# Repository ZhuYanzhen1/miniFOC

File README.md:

&nbsp;&nbsp;&nbsp;&nbsp;&nbsp;&nbsp;&nbsp;&nbsp;&nbsp;&nbsp;&nbsp;&nbsp;&nbsp;&nbsp;&nbsp;&nbsp;English / [中文](./README_CN.md)

&nbsp;&nbsp;&nbsp;&nbsp;Are you still buying a DC brush motor drive module in about 3<span>$</span>? Are you still worried about the high noise in addition to the already low response speed and life? Allow me to present you our project, miniFOC---- a FOC brushless motor control scheme that can get you the most bang for your buck, for just 3 <span>$</span>!  **miniFOC** has a built-in torque closed-loop controller so that you can control a brushless motor with a 3-wire UART port. The software and hardware design are fully compliant with the AGPL-3.0 open source license.

**Note: This branch is still in the development stage. The hardware circuit has been designed and tested to be stable, yet the firmware is still under development. After the development of this branch is completed, it will provide current loop and non-inductive FOC features. At the same time, version 1.x.x will reach end of life (EOL) and will no longer be maintained. Version 2.x.x will no longer provide any compatibility with version 1.x.x**

***

### Brief Introduction

&nbsp;&nbsp;&nbsp;&nbsp;This open-source project aims to accomplish a FOC(Field Oriented Control) scheme that is operatable with minimum costs in China. The components selected in the example circuit are all manufactured in China. FOC possesses various advantages when it comes to controlling BLCD (Brushless Direct Current) motor; some of the benefits are as follows:

1. FOC has no speed limit at all and can be accurately controlled at any speed
2. FOC excels at its reversing performance, ensuring the smoothness of forward and reverse switching even when running at its highest speed
3. FOC can perform braking control in the form of energy recovery.
4. FOC can achieve three closed-loop control of torque, speed, and position.
5. FOC has significantly lower noise but much higher efficiency compared that of electric regulation

&nbsp;&nbsp;&nbsp;Although FOC has many advantages, its large amount of calculation and complex principles requires an expensive controller, which made FOC unpopular. After half a year’s research and iteration, I deeply optimized the part of the code that implements mass calculations and re-selected its components to fit the domestic supply chain. I hope this open-source project can help domestic developers use BLDC motors with excellent performance and contribute to the open-source community.

&nbsp;&nbsp;&nbsp;&nbsp;Since the miniFOC 1.X.X version was launched earlier (September 2021), after two years, many component supply chains have changed, making the miniFOC v1.X.X hardware no longer adaptable to new needs. Therefore, I re-selected based on the domestic supply chain, and added current loop and non-inductive FOC functions based on the previous one.

***

### Comparison Of Open Source Solutions

|    Open source solution    |   **miniFOC v2**   | [simpleFOC v2.0.4](https://github.com/simplefoc/Arduino-SimpleFOCShield) | [ODrive v3.6](https://github.com/odriverobotics/ODrive) | [FpOC](https://github.com/WangXuan95/FpOC) |
| :------------------------: | :----------: | :----------------------------------------------------------: | :------------------------------------------------: | :------------------------------------------------: |
|      Microcontroller       | CH32V203C8T6 |                          ATmega328P                          |                   STM32F405RGT6                    |               FPGA |
|        Driver chip         |    BDR2L00    |                            L6234                             |                      DRV8301                       |                      MP6540                 |
|     PID loop frequency     |    20kHz (typical)    |                   1kHz (typical)                        |                        8kHz (typical)                        |                        18kHz (typical)                        |
| Whether have current loop |      Yes      |                              Yes                              |                        Yes                         |                        Yes                      |
|       Driving power        |     400W     |                             120W                             |                        960W                        |                        90W                        |
|    Cost price (approx.)    |     3$     |                             [15$](https://www.simplefoc.com/simplefoc_shield_product)                             |                        [259$](https://odriverobotics.com/shop/odrive-v36)                        |                        20$                        |

&nbsp;&nbsp;&nbsp;&nbsp;As can be seen from the table above, the solution adopted by **miniFOC** can achieve high performance at low cost. At the same time, due to the re-selection based on the domestic supply chain, the selection of devices is not so limited and provides many alternatives. When the driving power reaches 400W, the cost of FOC can be reduced to about 3$, which also proves the degree of cost optimization and huge potential of this project.

***

### Performance Parameter 

+ Input voltage range: 6V ~ 24V (you can modify the circuit according to the tutorial [here]() to adapt to higher voltage).
+ Maximum driving current: 30A (you can modify the circuit according to the tutorial [here]() to achieve greater driving current).
+ Detailed parameters of FOC: Current loop close loop control, SVPWM (Space Vector Pulse Width Modulation) is adopted.
+ Communication parameters: UART baud rate is 115200, and [Mid Capacity Data Transmit Protocol](https://github.com/ZhuYanzhen1/CDTP/blob/master/mdtp/README.md) is used for data transmission.
+ Microcontroller parameters: RV32IMACXW core, 144MHz frequency, 64KB FLASH, 20KB SRAM. 

***

### Function Features

+ [x] Using space vector pulse width modulation
+ [x] Torque control without current sensor
+ [x] Rotational speed closed loop control
+ [x] Rotation angle closed loop control
+ [x] Automatic phase sequence detection and correction
+ [ ] Current loop closed loop control
+ [ ] Sensorless FOC algorithm

***

### Development Environment 

+ EDA Tool: KiCAD 7.0.8 (VC++ 1936, 64bit)
+ Compiler tool chain: riscv-none-elf-gcc 12.2.0 or riscv-none-embed-gcc 8.2.0
+ Programming tool: OpenOCD 0.11.0+dev-gfad123a16- (2023-07-03-15:11)
+ Integrated development tools: CLion 2023.2.2 #CL-232.9921.42
+ Software development tools: Qt 5.14.2 (MinGW 7.3.0 64bit)
+ Operating system and tool chain: 
  + Win10 + MinGW + CLion + riscv-none-elf-gcc + OpenOCD
  + Ubuntu22.04 + make + cmake + riscv-none-embed-gcc + OpenOCD

***

### Getting Started

+ You can visit the [Wiki page](https://github.com/ZhuYanzhen1/miniFOC/wiki) of this project for a getting started guide.
+ You can visit [Github Page](https://zhuyanzhen1.github.io/miniFOC/) to learn about the functions and variable usage in the code.
+ You can visit the [Release](https://github.com/ZhuYanzhen1/miniFOC/releases) page to get the latest firmware, monitor tools, and compilation tool chains.

***

### Bugs & Feature Requests

Please report bugs and request features using the [Issue Tracker](https://github.com/ZhuYanzhen1/miniFOC/issues) and follow these request:

1. Before publishing an Issue, please check whether the existing Issue contains your question or request. If so, please try to solve it first according to the solution in the Issue.
2. When publishing an Issue, please provide your operating environment and write down the reproduction method in detail.
3. For discussions on non-operational bugs, please start them in [Discussion](https://github.com/ZhuYanzhen1/miniFOC/discussions) and do not submit them to Issues.

***

### License

The source code is released under a [AGPL-3.0 License](https://github.com/ZhuYanzhen1/miniFOC/blob/main/LICENSE).

**Affiliation：AcmeTech<br>
Author: Yanzhen Zhu<br>
Maintainer：YanzhenZhu, 2208213223@qq.com**

&nbsp;&nbsp;&nbsp;&nbsp;The project has been tested under Windows 10 and Ubuntu 22.04 LTS. This is research code, expect that it changes often and any fitness for a particular purpose is disclaimed.

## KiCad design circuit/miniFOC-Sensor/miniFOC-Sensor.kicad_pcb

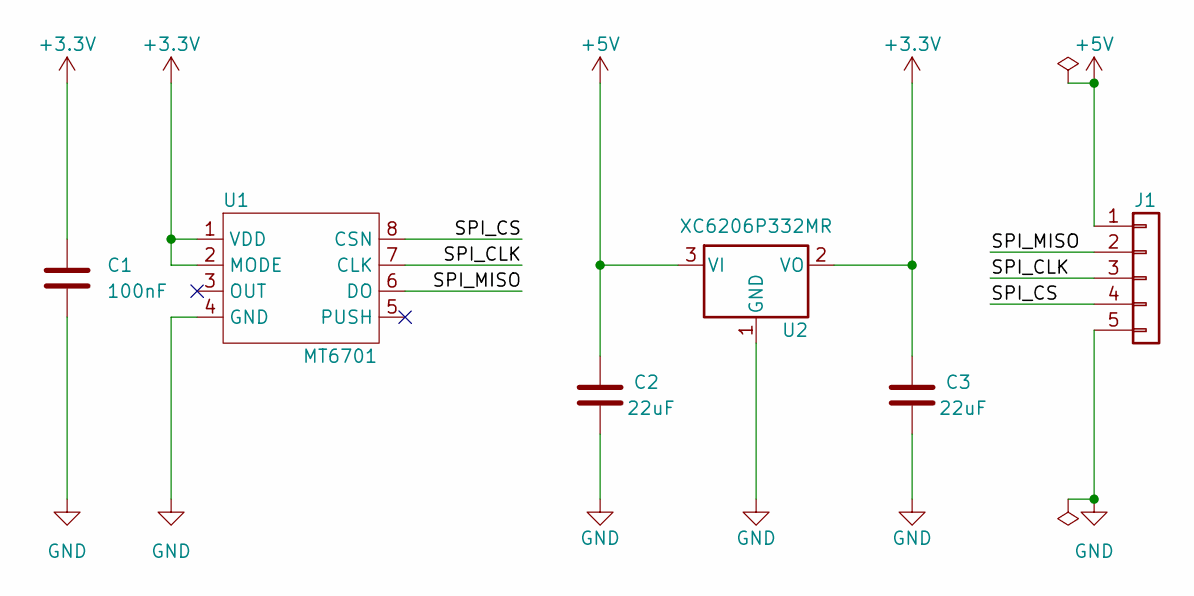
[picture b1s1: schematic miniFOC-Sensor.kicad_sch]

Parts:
C1: 100nF; C_0402_1005Metric
C2, C3: 22uF; C_0603_1608Metric
J1: Conn_01x05; JST_GH_SM05B-GHS-TB_1x05-1MP_P1.25mm_Horizontal
U1: MT6701; SOP-8_3.9x4.9mm_P1.27mm
U2: XC6206P332MR; SOT-23

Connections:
+3.3V: C1.1, C3.2, U1.1 (VDD), U1.2 (MODE), U2.2 (VO)
+5V: C2.2, J1.1, U2.3 (VI)
/SPI_CLK: J1.3, U1.7 (CLK)
/SPI_CS: J1.4, U1.8 (CSN)
/SPI_MISO: J1.2, U1.6 (DO)
GND: C1.2, C2.1, C3.1, J1.5, U1.4 (GND), U2.1 (GND)

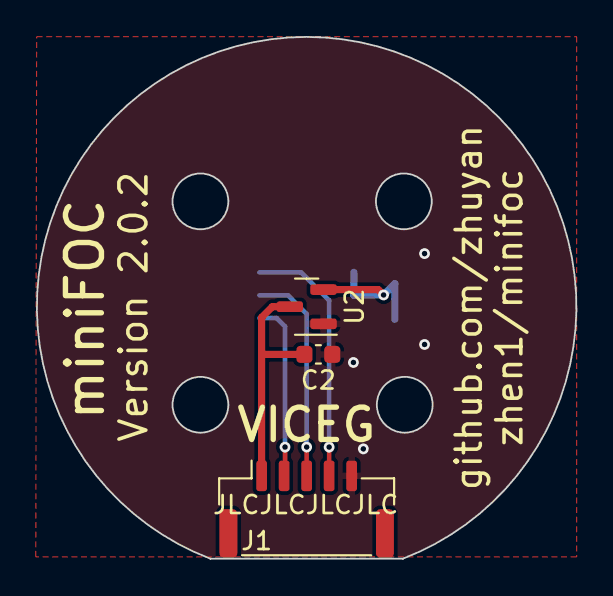
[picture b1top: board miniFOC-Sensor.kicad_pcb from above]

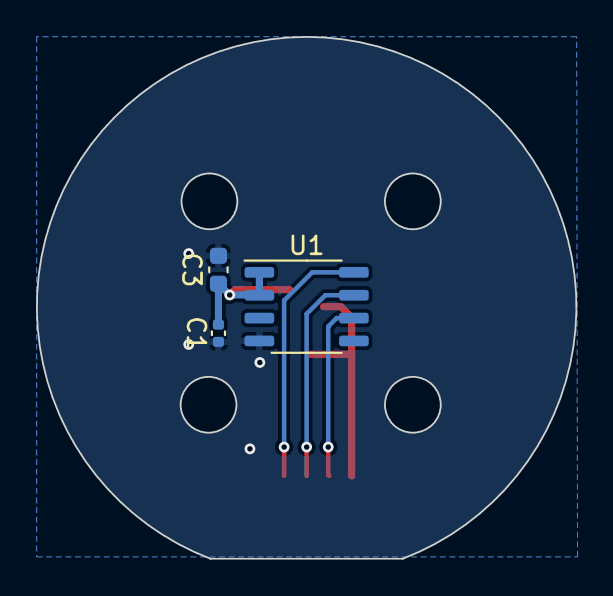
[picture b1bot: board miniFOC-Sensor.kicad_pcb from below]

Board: 2 copper layers, 30.0 x 29.0 mm, 6 parts (3 on the bottom side), 6 nets.

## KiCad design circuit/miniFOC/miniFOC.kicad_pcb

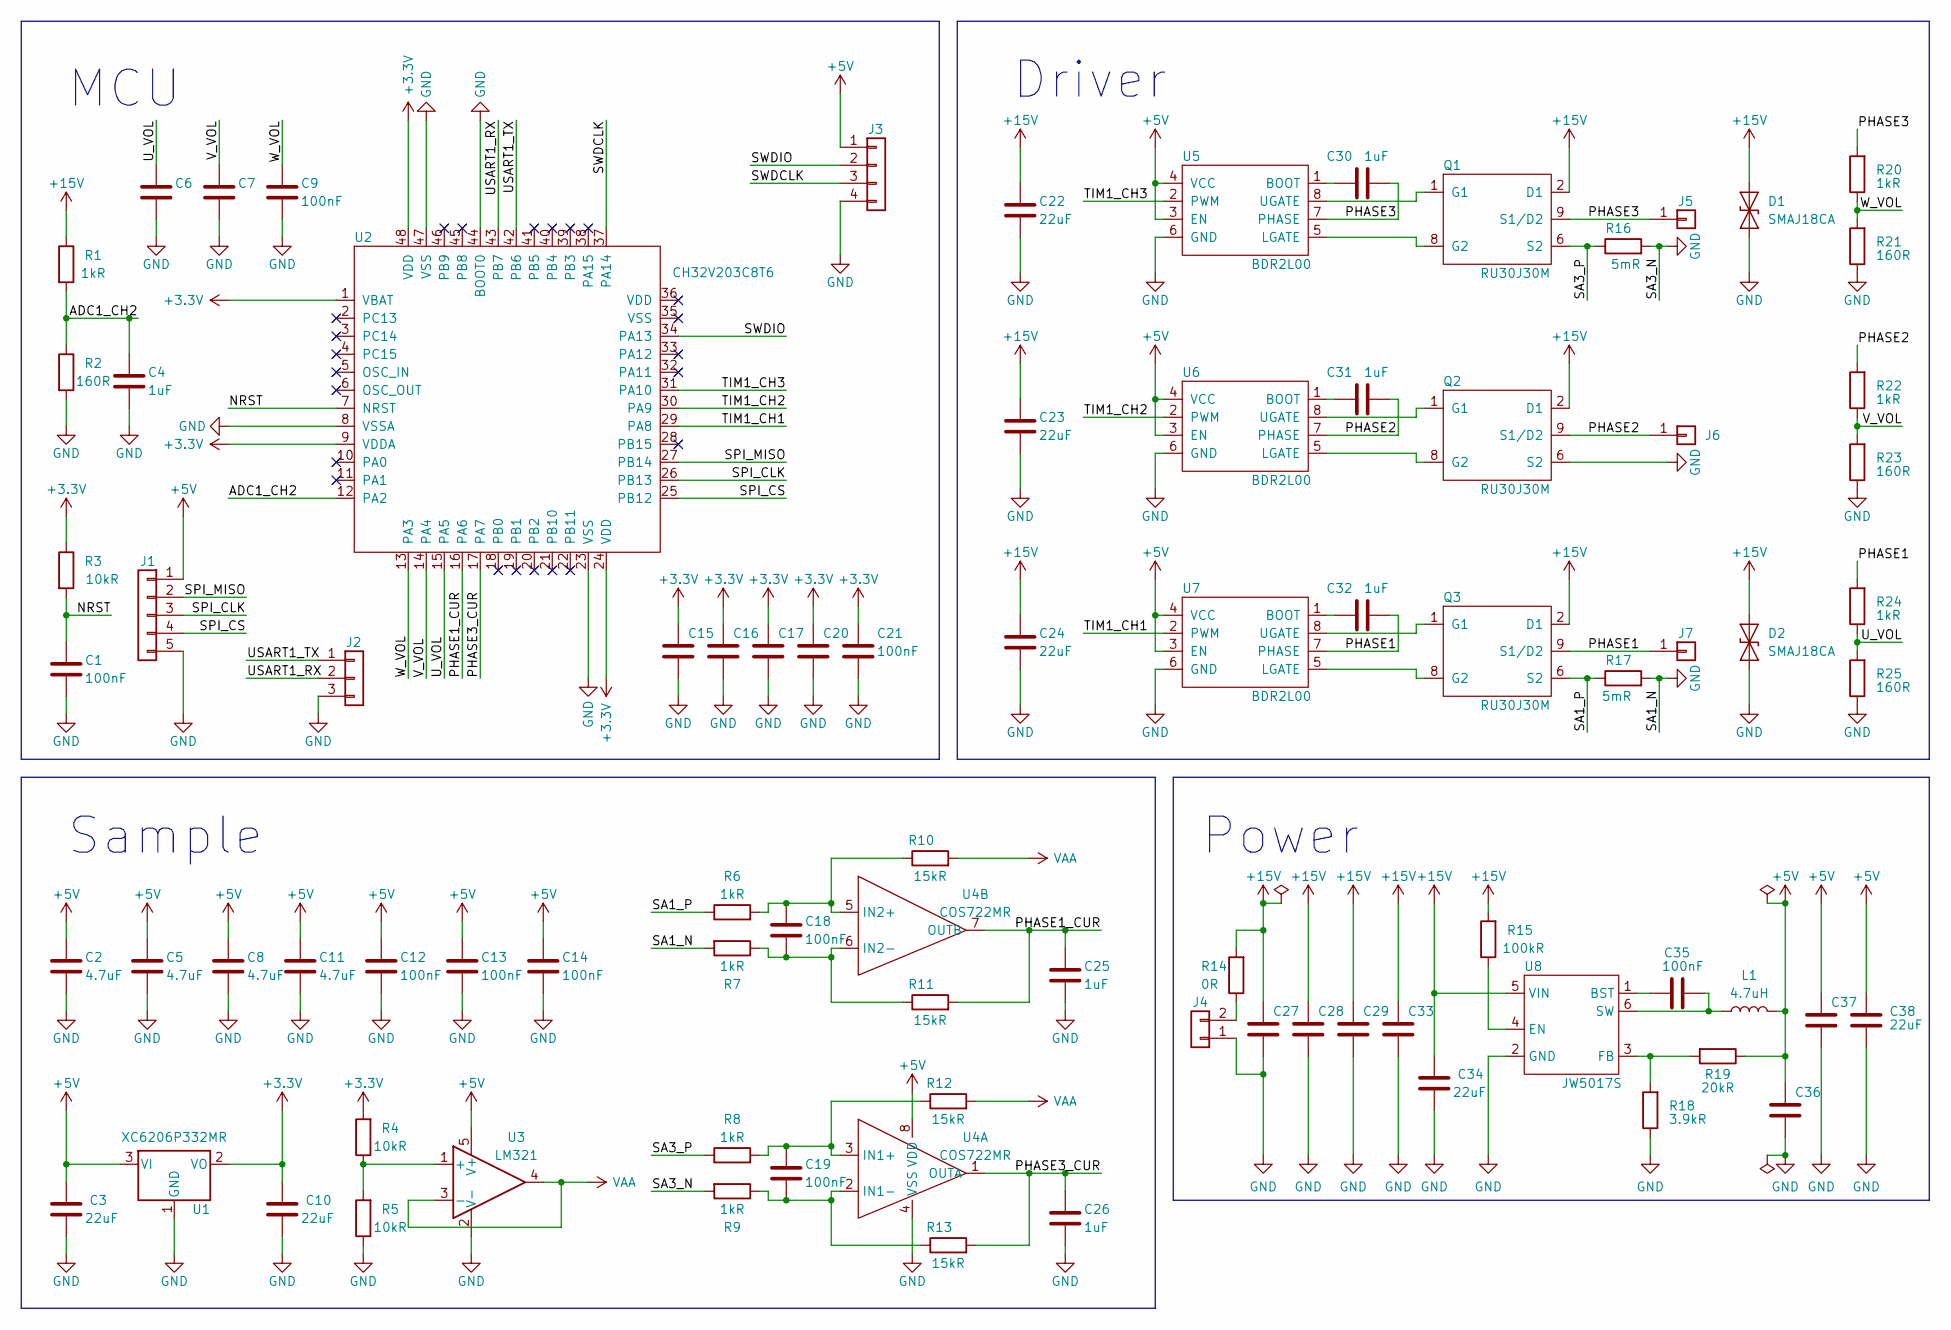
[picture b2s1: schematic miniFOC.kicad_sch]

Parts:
C1, C6, C7, C9, C12, C13, C14, C15, C16, C17, C18, C19, C20, C21: 100nF; C_0402_1005Metric
C2, C5, C8, C11: 4.7uF; C_0402_1005Metric
C3, C10, C36, C37, C38: 22uF; C_0603_1608Metric
C4, C25, C26, C30, C31, C32: 1uF; C_0402_1005Metric
C22, C23, C24, C27, C28, C29, C33, C34: 22uF; C_0805_2012Metric
C35: 100nF; C_1206_3216Metric
D1, D2: SMAJ18CA; D_SMB
J1: Conn_01x05; Pad_5
J2: Conn_01x03; JST_GH_SM03B-GHS-TB_1x03-1MP_P1.25mm_Horizontal
J3: Conn_01x04; Pad_4
J4: Conn_01x02; SolderWire-0.1sqmm_1x02_P3.6mm_D0.4mm_OD1mm
J5, J6, J7: Conn_01x01; Pad_1
L1: 4.7uH; L_Coilcraft_XxL4040
Q1, Q2, Q3: RU30J30M; PDFN-8_L5.8-W4.9_RU30J30M
R1, R6, R7, R8, R9, R20, R22, R24: 1kR; R_0402_1005Metric
R2, R21, R23, R25: 160R; R_0402_1005Metric
R3, R4, R5: 10kR; R_0402_1005Metric
R10, R11, R12, R13: 15kR; R_0402_1005Metric
R14: 0R; R_1812_4532Metric
R15: 100kR; R_0402_1005Metric
R16, R17: 5mR; R_1206_3216Metric
R18: 3.9kR; R_0402_1005Metric
R19: 20kR; R_0402_1005Metric
U1: XC6206P332MR; SOT-23
U2: CH32V203C8T6; LQFP-48_7x7mm_P0.5mm
U3: LM321; SOT-23-5
U4: COS722MR; MSOP-8_3x3mm_P0.65mm
U5, U6, U7: BDR2L00; TDFN-8_L2.0-W2.0-P0.50-BL-EP
U8: JW5017S; SOT-23-6

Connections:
+3.3V: C10.2, C15.1, C16.1, C17.1, C20.1, C21.1, R3.1, R4.2, U1.2 (VO), U2.1 (VBAT), U2.9 (VDDA), U2.24 (VDD), U2.48 (VDD)
+5V: C2.1, C3.2, C5.1, C8.1, C11.1, C12.1, C13.1, C14.1, C36.2, C37.2, C38.2, J1.1, J3.1, L1.2, R19.1, U1.3 (VI), U3.5 (V+), U4.8 (VDD), U5.3 (EN), U5.4 (VCC), U6.3 (EN), U6.4 (VCC), U7.3 (EN), U7.4 (VCC)
+15V: C22.2, C23.2, C24.2, C27.2, C28.2, C29.2, C33.2, C34.2, D1.2 (A2), D2.2 (A2), Q1.2 (D1), Q1.3 (D1), Q1.4 (D1), Q2.2 (D1), Q2.3 (D1), Q2.4 (D1), Q3.2 (D1), Q3.3 (D1), Q3.4 (D1), R1.1, R14.2, R15.2, U8.5 (VIN)
/ADC1_CH2: C4.1, R1.2, R2.1, U2.12 (PA2)
/NRST: C1.1, R3.2, U2.7 (NRST)
/PHASE1: C32.2, J7.1, Q3.9 (S1/D2), R24.2, U7.7 (PHASE)
/PHASE1_CUR: C25.1, R11.2, U2.16 (PA6), U4.7 (OUTB)
/PHASE2: C31.2, J6.1, Q2.9 (S1/D2), R22.2, U6.7 (PHASE)
/PHASE3: C30.2, J5.1, Q1.9 (S1/D2), R20.2, U5.7 (PHASE)
/PHASE3_CUR: C26.1, R13.2, U2.17 (PA7), U4.1 (OUTA)
/SA1_P: Q3.5 (S2), Q3.6 (S2), Q3.7 (S2), R6.1, R17.1
/SA3_P: Q1.5 (S2), Q1.6 (S2), Q1.7 (S2), R8.1, R16.1
/SPI_CLK: J1.3, U2.26 (PB13)
/SPI_CS: J1.4, U2.25 (PB12)
/SPI_MISO: J1.2, U2.27 (PB14)
/SWDCLK: J3.3, U2.37 (PA14)
/SWDIO: J3.2, U2.34 (PA13)
/TIM1_CH1: U2.29 (PA8), U7.2 (PWM)
/TIM1_CH2: U2.30 (PA9), U6.2 (PWM)
/TIM1_CH3: U2.31 (PA10), U5.2 (PWM)
/USART1_RX: J2.2, U2.43 (PB7)
/USART1_TX: J2.1, U2.42 (PB6)
/U_VOL: C6.1, R24.1, R25.2, U2.15 (PA5)
/V_VOL: C7.1, R22.1, R23.2, U2.14 (PA4)
/W_VOL: C9.1, R20.1, R21.2, U2.13 (PA3)
GND: C1.2, C2.2, C3.1, C4.2, C5.2, C6.2, C7.2, C8.2, C9.2, C10.1, C11.2, C12.2, C13.2, C14.2, C15.2, C16.2, C17.2, C20.2, C21.2, C22.1, C23.1, C24.1, C25.2, C26.2, C27.1, C28.1, C29.1, C33.1, C34.1, C36.1, C37.1, C38.1, D1.1 (A1), D2.1 (A1), J1.5, J2.3, J3.4, J4.1, Q2.5 (S2), Q2.6 (S2), Q2.7 (S2), R2.2, R5.1, R7.2, R9.2, R16.2, R17.2, R18.1, R21.1, R23.1, R25.1, U1.1 (GND), U2.8 (VSSA), U2.23 (VSS), U2.44 (BOOT0), U2.47 (VSS), U3.2 (V-), U4.4 (VSS), U5.6 (GND), U5.9 (EP), U6.6 (GND), U6.9 (EP), U7.6 (GND), U7.9 (EP), U8.2 (GND)
unnamed: J4.2, R14.1
unnamed: Q1.1 (G1), U5.8 (UGATE)
unnamed: Q1.8 (G2), U5.5 (LGATE)
unnamed: Q2.1 (G1), U6.8 (UGATE)
unnamed: Q2.8 (G2), U6.5 (LGATE)
unnamed: Q3.1 (G1), U7.8 (UGATE)
unnamed: Q3.8 (G2), U7.5 (LGATE)
unnamed: R4.1, R5.2, U3.1 (+)
unnamed: C19.1, R8.2, R12.1, U4.3 (IN1+)
unnamed: C19.2, R9.1, R13.1, U4.2 (IN1-)
unnamed: C18.1, R6.2, R10.1, U4.5 (IN2+)
unnamed: C18.2, R7.1, R11.1, U4.6 (IN2-)
unnamed: C30.1, U5.1 (BOOT)
unnamed: C31.1, U6.1 (BOOT)
unnamed: C32.1, U7.1 (BOOT)
unnamed: C35.2, U8.1 (BST)
unnamed: R15.1, U8.4 (EN)
unnamed: R18.2, R19.2, U8.3 (FB)
unnamed: C35.1, L1.1, U8.6 (SW)
VAA: R10.2, R12.2, U3.3 (-), U3.4

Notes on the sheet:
MCU
Sample
Driver
Power

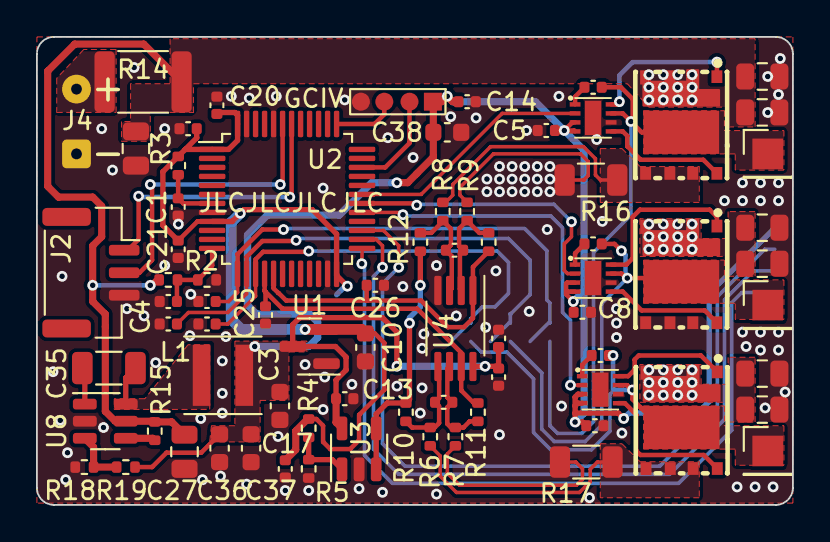
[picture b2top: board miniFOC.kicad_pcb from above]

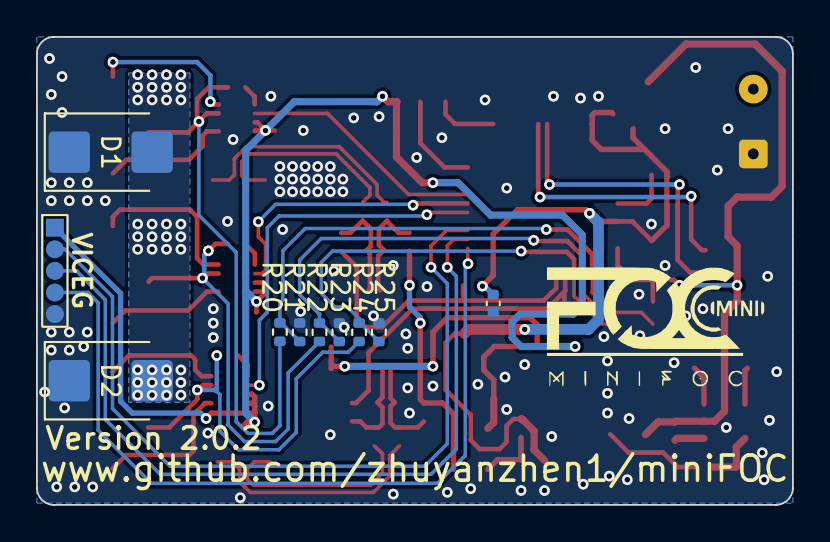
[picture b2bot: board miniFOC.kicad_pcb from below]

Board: 2 copper layers, 42.0 x 26.0 mm, 84 parts (10 on the bottom side), 46 nets.

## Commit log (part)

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2021-08-13 add README_CN
2021-08-13 add title in readme
2021-08-13 add LICENSE in readme
2021-08-13 add Bugs and feature requests in readme
2021-08-14 add schematic of lceda for circuit and add schematic image
2021-08-14 renew schematic for circuit
2021-08-14 add PCB for circuit
2021-08-14 add Performance Parameter and Comparison Of Open Source Solutions in README
2021-08-16 Add a summary to Readme
2021-08-16 Repair some display bugs in README
2021-08-17 Add the official library function file to the program folder.
2021-08-17 Add CMakeLists in program directory.
2021-08-17 Modified cmakelists file, added link file and migrated startup file. Optimized library
2021-08-17 Optimize library codes and change position for README sumarry
2021-08-17 Create cmake.yml
    add github action workflow
2021-08-17 Renew cmake.yml file
2021-08-17 Repair environment bugs in cmake.yml
2021-08-17 Add artifact and renew compiler for actions
2021-08-17 repair artifact syntax bug
2021-08-17 Add docs dir for github page testing
2021-08-17 Add deploy stage for ci
2021-08-17 Add temp jekyll site for github page
2021-08-17 fix stage bugs for ci
2021-08-17 renew some info in github page
2021-08-17 change index type to page
2021-08-18 renew miniFOC PCB files and manufacture files
2021-08-19 add logo for minifoc
2021-08-19 modify README, centering version logo
2021-08-19 modify ci stratergy
2021-08-19 add gitee mirror address to README
2021-08-21 modify cmakelists link library to optimize ram size
2021-08-21 modify github page index file
2021-08-21 add firmware submodule from gitee
2021-08-21 add trig condition on push event in cmake.yml
2021-08-21 add env to transform gitee_key
2021-08-21 add GIT_SSH_COMMAND to cmake.yml
2021-08-21 change compile action runtime to 21:00 UTC8
2021-08-21 Move the image folder to the docs folder, modify the continuous integration file, create a folder and add an issue template before uploading.
2021-08-21 modify issue template
2021-08-21 Update new firmware link to Github Pages
2021-08-21 Modify the commit acquisition method
2021-08-21 It fully realizes the functions of automatic compilation and automatic deployment to GitHub pages.
2021-08-23 Add miniFOC Sensor manufacture files to manufacture dir
2021-08-23 Add macro definition of LED level toggle.
2021-08-23 Add compile firmware scratch on windows for program.
2021-08-24 add miniFOC-Sensor schematic image
2021-08-24 add cmake install image
2021-08-25 change windows_check_install image size
2021-08-25 add ubuntu check image to docs
2021-08-25 modify cmake required version to 3.16
2021-08-25 modify links in readme in firmware directory
2021-08-25 Complete the unpacking program of finite state machine for medium capacity data transmission protocol.
2021-08-25 Adjust the comments of some files to make the format more standardized
2021-08-26 Add the packet function of medium capacity transmission protocol. When the data packet is received, it is sent back according to the original packet to test whether the function of receiving and send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
2021-08-28 Add wiki repo into docs directory
2021-08-28 Add Timer1 initialization code to output PWM
2021-08-30 The inverse Clarke transform and SVP width modulation algorithm in FOC algorithm are added.
2021-08-30 Modify the estimated completion date of the project
2021-08-30 Code comments are added for fast mathematical calculation functions and FOC calculation functions.
2021-09-02 The programming of spi0 peripheral initialization program and function annotation are completed.
2021-09-02 Add read and initialization functions of magnetic encoder. Add comments for SPI related functions and move SPI frequency division coefficient to config file for configuration.
2021-09-02 Adjust PWM to 10kHz to prevent MOSFET from heating and serious burning. The PWM frequency calculation function is modified.
2021-09-03 change auto compile time to 23:50
2021-09-03 modify readme microcontroller frequency
2021-09-03 The electric angle correction program is added. The pole number and encoder resolution are added to the config file for modification. Corrected PWM initialization duty cycle to prevent power on burn 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
2021-09-03 update wiki page repo
2021-09-03 Update the PCB and manufacturing files of the sensor board, and fix the problem of interface image.
2021-09-03 Polish REAMDE
2021-09-04 The closed-loop frequency data of each open source project is modified.
2021-09-05 Fix the important error of magnetic encoder reading program, namely SPI timing problem. The initialization program of magnetic encoder is deleted, and initialization is not required.
2021-09-05 Add comments for the interrupt service function. Add speed calculation function.
2021-09-06 The bottom function of reading and writing internal flash is added. This function is not perfect and needs to be tested.
2021-09-06 Add comments for internal flash read / write functions.
2021-09-06 Normalized FLASH read / write function name.
2021-09-07 Modify the motor phase sequence correction algorithm, speed up the correction process and add protection measures.
2021-09-07 Fix mdtp_callback_handler function name mismatch.
2021-09-08 Change the flash write function to a function that can be written continuously.
2021-09-08 Modify the flash read-write function name, and the flash read-write function test is successful.
2021-09-09 The program of saving correction parameters in flash is realized. The correction and start rotation are controlled through the serial port.
2021-09-09 Add upper computer monitor tools for miniFOC
2021-09-09 The unpacking program of medium capacity data transfer protocol was successfully transplanted to monitor tool.
2021-09-10 Add QCustomPlot to monitor tool
2021-09-10 Add speed angle data analyzer for monitor.
2021-09-10 Modify the report buffer initialization location
2021-09-10 Add "calibrate" and "start / stop" control buttons and realize their functions.
2021-09-10 Add PID control algorithm and initialize the PID structure of speed loop and angle loop.
2021-09-10 Add comments for LED related macro definitions.
2021-09-10 Modify the fast cosine calculation function to the macro definition implementation. Macro definition of fast clipping is added.
2021-09-11 Adding different closed-loop codes has not been tested. Add program segments and commands to stop the motor.
2021-09-11 Realize the function of sending stop command by pressing the stop button.
2021-09-11 Add a comment for timer deactivation.
2021-09-12 Modify control package to package 0
2021-09-12 Modify the control package ID in the monitor tool and realize the selection and switching of torque, speed and angle control modes.
2021-09-12 Fixed the problem that the reverse speed could not be measured during speed calculation.
2021-09-12 The circuit of minifoc is modified to separate the debug interface from the UART interface.
2021-09-13 The PCB circuit of minifoc is modified
2021-09-15 Add angle loop PID parameter configuration command.
2021-09-16 Add textbox to set minimum and maxinum of user expect slider
2021-09-16 modify widgets arrange and place a tabcontainer to adjust parameter
2021-09-16 Add speed update configure macro to config.h.
2021-09-18 Add speed loop PID debugging control for monitor.
2021-09-18 Add angle loop PID debugging control for monitor. And increase the maximum integral value to set the slider.
2021-09-19 Fixed a problem with the default value of the text box.
2021-09-20 Add the callback function for the change of speed loop PID parameter adjustment slider value, and modify the packet sending function to send different Zhi according to the change of different sliders
2021-09-20 Add the callback function for the change of angle loop PID parameter adjustment slider value. Add a few comments to the monitor code.
2021-09-21 A limiting function is added to the low-pass filter.
2021-09-22 The validity judgment of PID parameters is added to prevent incorrect PID parameters from being used when PID parameters are not configured.
2021-09-22 Modify the development environment version in readme and add notes for the image repo.
2021-09-24 The lower computer realizes the complete parameter upload function.
2021-09-24 The problem of sending messages after the monitor is started has been solved. The problem of enabling logic of slider control in monitor is solved.
2021-09-26 Change the judgment of the monitor after receiving the packet into a switch statement.
2021-09-26 Add the slider position and the maximum and minimum value change code for the monitor. Now the parameters of the motor can be parsed and reflected on the slider.
2021-09-29 Add comments for PID program.
2021-10-04 Correct the medium capacity data transfer protocol link in README.
2021-10-08 Change the Doxygen annotation of CMSIS file to unified style.
2021-10-09 Change the file comment to a type recognized by Doxygen.
2021-10-09 Doxygen configuration file is added, which can generate documents directly through the configuration file.
2021-10-09 Modify the main page of Doxygen generated documents to readme file as the main page.
2021-10-11 add two lables in monitor
2021-10-20 Modify the GitHub action timed automatic compilation firmware to compile only when push occurs.
2021-10-29 Modify the page content of GitHub page so that GitHub page is mainly used to display Doxygen documents.
2021-10-29 Generate the Doxygen document and add it to the docs folder so that it can be displayed in the GitHub page.
2021-10-29 The circuit is updated to solve the problem of burnout when the input voltage exceeds the Vgs voltage.
2021-11-04 The display and upload of available information are realized.
2021-11-04 Added the button and method of flash writing content control. There are still problems with parameter reading and slider display that need to be modified.
2021-11-06 Modify the version number in readme and add fpoc as the comparison item.
2022-05-24 Updated the README file.
2022-05-24 Updated the firmware repository location.
2022-05-24 Close auto mirror to gitee
2022-08-02 Update the content and links on the Doxygen homepage
2022-08-02 Update comments on code files
2022-08-02 Update Doxygen documentation
2022-10-04 Complete the miniFOC-Sensor schematic drawing.
2022-10-07 The design of the miniFOC circuit schematic is basically completed.
2022-10-10 Finished new miniFOC schematic design.
2022-10-21 Completed PCB drawing of miniFOC sensor board
2022-11-12 Complete the circuit and PCB design for version 2.0.
2023-06-18 Modify readme
2023-06-18 Create template program project
2023-06-24 Modify the sampling resistor package in the schematic diagram and PCB, and change its resistance value to 5 milliohms to adapt to the current sampling range of 20A.
2023-08-11 Fix bugs in total_machine_angle calculate and pid integer anti-constrain method.
2023-10-05 The test UART1 output is successful and the PWM output is successful.
2023-10-09 Completed the initialization code for the ADC peripherals, not tested yet.
2023-10-09 rearrange doc images and resources, add pack scripts for monitor tools.
2023-10-09 Add scripts to configure and make program on linux.
2023-10-11 Converting floating-point arithmetic to fixed-point arithmetic remains an unresolved problem.
2023-10-13 Update the library functions to the latest version, add SPI2 read and write functions, and initialize the TIM3 timer.
2023-10-14 Change all variables to the standard variable types defined by stdint, add flash reading and writing functions, and complete the test. Move the serial port transceiver interrupt processing function t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
2023-10-14 Updated the version number of the sensor board and adjusted the silk screen position in the PCB.
2023-10-14 Updated the readme file and added an interaction protocol definition file.
2023-10-14 Modify the readme file
2023-10-15 Migrate the medium-capacity transmission protocol and fix the issue of serial port idle receive interrupt delay of one cycle.
2023-11-09 Modify the appearance of the miniFOC sensor board to use Edge Cuts layer defines holes.

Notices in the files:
README.md:
License: AGPL
